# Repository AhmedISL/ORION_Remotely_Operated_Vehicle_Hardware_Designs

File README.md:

# ORION Remotely Operated Vehicle Hardware Design

These are the printed circuit boards (PCBs) designed for controlling the Remotely Operated Vehicle (ROV) which participated in the MATE international ROV competition 2019 and won the 7th place internationally and the 1st place locally and regionally.

## The electrical system is integrated using 4 main PCBs:
> ###### 1- **2** PCBs for the power management.
> ###### 2- **2** PCBs for the communication system and actuators' control.

***Power management PCBs' specifications:***
> ###### 1- Single layer.
> ###### 2- Voltage input range from 48V to 36V. 
> ###### 3- Over-current, voltage and thermal safety system

***Communication and actuators' control PCBs' specification:***
> ###### 1- Single layer.
> ###### 2- Voltage input range from 12V to 9V.
> ###### 3- The required voltage output with 99% efficiency
> ###### 4- Data transferring capability over Bluetooth/USB serial.

# Electronics' Enclosure Assembly

# Board I

# Board II

# Board 2

# Board 3

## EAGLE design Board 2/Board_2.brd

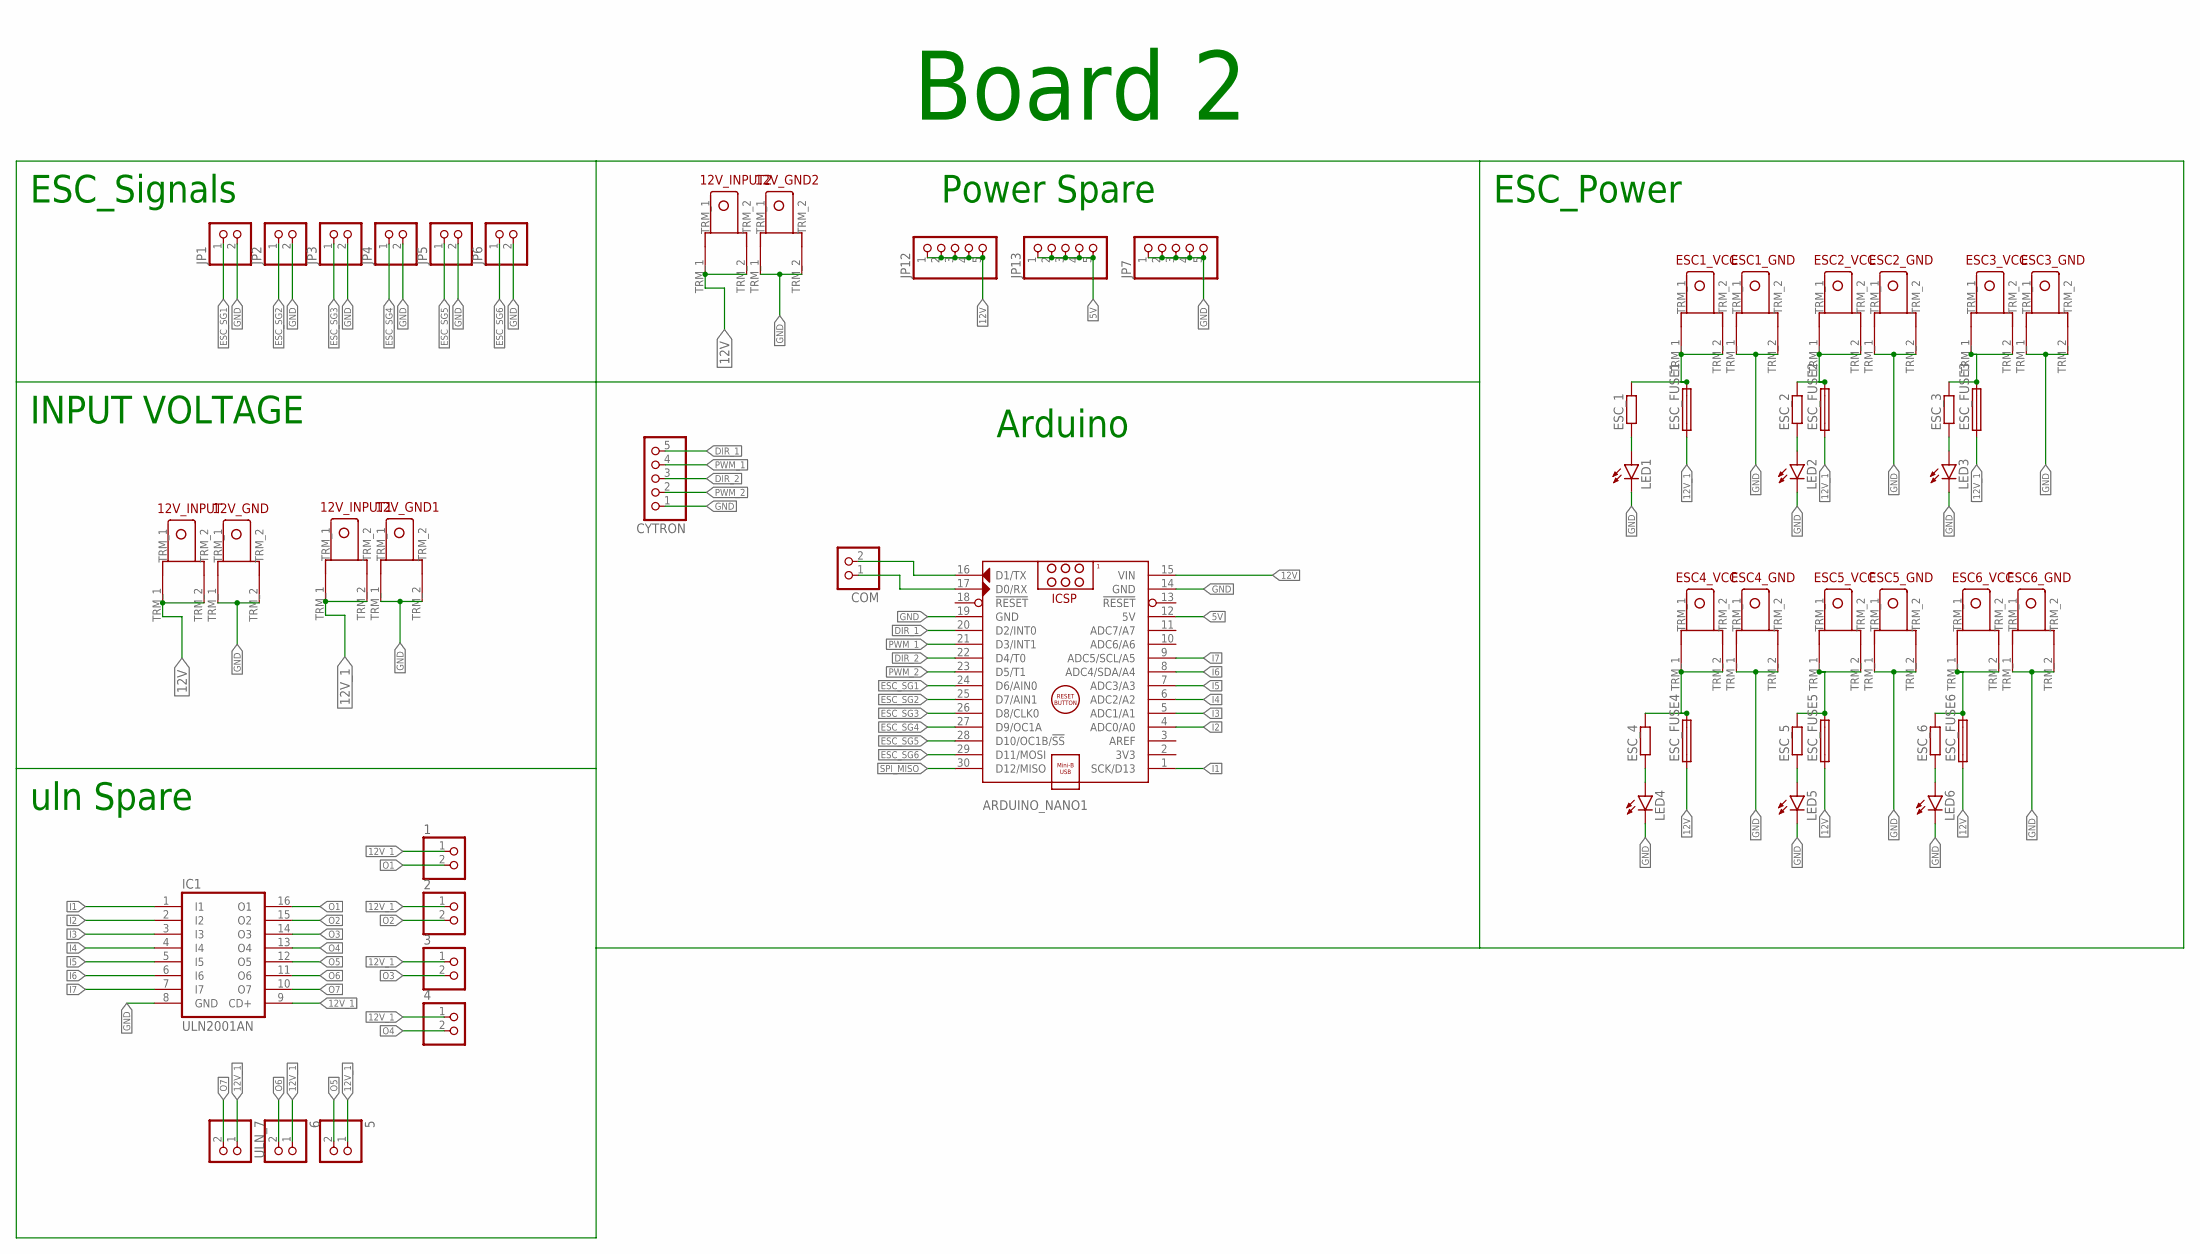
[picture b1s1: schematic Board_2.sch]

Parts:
1, 2, 3, 4, 5, 6: PINHD-1X2; 1X02
12V_GND, 12V_GND1, 12V_GND2, 12V_INPUT, 12V_INPUT1, 12V_INPUT2: TERMINAL_EDITED
ARDUINO_NANO1: ARDUINO_NANO
COM: PINHD-1X2; 1X02
CYTRON: PINHD-1X5; 1X05
ESC1_GND, ESC1_VCC, ESC2_GND, ESC2_VCC, ESC3_GND, ESC3_VCC, ESC4_GND, ESC4_VCC, ESC5_GND, ESC5_VCC, ESC6_GND, ESC6_VCC: TERMINAL_EDITED
ESC_1, ESC_2, ESC_3, ESC_4, ESC_5, ESC_6: RESISTOR; 0207/10
ESC_FUSE1, ESC_FUSE2, ESC_FUSE3, ESC_FUSE4, ESC_FUSE5, ESC_FUSE6: FUSE; SH22,5A
IC1: ULN2001AN; DIL16
JP1, JP2, JP3, JP4, JP5, JP6: PINHD-1X2; 1X02
JP7, JP12, JP13: PINHD-1X5; 1X05
LED1, LED2, LED3, LED4, LED5, LED6: LED5MM
ULN_7: PINHD-1X2; 1X02

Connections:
5V: ARDUINO_NANO1.12 (5V), JP13.1, JP13.2, JP13.3, JP13.4, JP13.5
12V: 12V_INPUT.TRM_1, 12V_INPUT.TRM_2, 12V_INPUT2.TRM_1, 12V_INPUT2.TRM_2, ARDUINO_NANO1.15 (VIN), ESC_FUSE4.1, ESC_FUSE5.1, ESC_FUSE6.1, JP12.1, JP12.2, JP12.3, JP12.4, JP12.5
12V_1: 1.1, 2.1, 3.1, 4.1, 5.1, 6.1, 12V_INPUT1.TRM_1, 12V_INPUT1.TRM_2, ESC_FUSE1.1, ESC_FUSE2.1, ESC_FUSE3.1, IC1.9 (CD+), ULN_7.1
DIR_1: ARDUINO_NANO1.20 (D2/INT0), CYTRON.5
DIR_2: ARDUINO_NANO1.22 (D4/T0), CYTRON.3
ESC_SG1: ARDUINO_NANO1.24 (D6/AIN0), JP1.1
ESC_SG2: ARDUINO_NANO1.25 (D7/AIN1), JP2.1
ESC_SG3: ARDUINO_NANO1.26 (D8/CLK0), JP3.1
ESC_SG4: ARDUINO_NANO1.27 (D9/OC1A), JP4.1
ESC_SG5: ARDUINO_NANO1.28 (D10/OC1B/!SS), JP5.1
ESC_SG6: ARDUINO_NANO1.29 (D11/MOSI), JP6.1
GND: 12V_GND.TRM_1, 12V_GND.TRM_2, 12V_GND1.TRM_1, 12V_GND1.TRM_2, 12V_GND2.TRM_1, 12V_GND2.TRM_2, ARDUINO_NANO1.14 (GND), ARDUINO_NANO1.19 (GND), CYTRON.1, ESC1_GND.TRM_1, ESC1_GND.TRM_2, ESC2_GND.TRM_1, ESC2_GND.TRM_2, ESC3_GND.TRM_1, ESC3_GND.TRM_2, ESC4_GND.TRM_1, ESC4_GND.TRM_2, ESC5_GND.TRM_1, ESC5_GND.TRM_2, ESC6_GND.TRM_1, ESC6_GND.TRM_2, IC1.8 (GND), JP1.2, JP2.2, JP3.2, JP4.2, JP5.2, JP6.2, JP7.1, JP7.2, JP7.3, JP7.4, JP7.5, LED1.K (C), LED2.K (C), LED3.K (C), LED4.K (C), LED5.K (C), LED6.K (C)
I1: ARDUINO_NANO1.1 (SCK/D13), IC1.1 (I1)
I2: ARDUINO_NANO1.4 (ADC0/A0), IC1.2 (I2)
I3: ARDUINO_NANO1.5 (ADC1/A1), IC1.3 (I3)
I4: ARDUINO_NANO1.6 (ADC2/A2), IC1.4 (I4)
I5: ARDUINO_NANO1.7 (ADC3/A3), IC1.5 (I5)
I6: ARDUINO_NANO1.8 (ADC4/SDA/A4), IC1.6 (I6)
I7: ARDUINO_NANO1.9 (ADC5/SCL/A5), IC1.7 (I7)
unnamed: ESC1_VCC.TRM_1, ESC1_VCC.TRM_2, ESC_1.2, ESC_FUSE1.2
unnamed: ESC2_VCC.TRM_1, ESC2_VCC.TRM_2, ESC_2.2, ESC_FUSE2.2
unnamed: ARDUINO_NANO1.17 (D0/RX), COM.1
unnamed: ARDUINO_NANO1.16 (D1/TX), COM.2
unnamed: ESC3_VCC.TRM_1, ESC3_VCC.TRM_2, ESC_3.2, ESC_FUSE3.2
unnamed: ESC4_VCC.TRM_1, ESC4_VCC.TRM_2, ESC_4.2, ESC_FUSE4.2
unnamed: ESC_1.1, LED1.A
unnamed: ESC5_VCC.TRM_1, ESC5_VCC.TRM_2, ESC_5.2, ESC_FUSE5.2
unnamed: ESC_2.1, LED2.A
unnamed: ESC6_VCC.TRM_1, ESC6_VCC.TRM_2, ESC_6.2, ESC_FUSE6.2
unnamed: ESC_3.1, LED3.A
unnamed: ESC_4.1, LED4.A
unnamed: ESC_5.1, LED5.A
unnamed: ESC_6.1, LED6.A
O1: 1.2, IC1.16 (O1)
O2: 2.2, IC1.15 (O2)
O3: 3.2, IC1.14 (O3)
O4: 4.2, IC1.13 (O4)
O5: 5.2, IC1.12 (O5)
O6: 6.2, IC1.11 (O6)
O7: IC1.10 (O7), ULN_7.2
PWM_1: ARDUINO_NANO1.21 (D3/INT1), CYTRON.4
PWM_2: ARDUINO_NANO1.23 (D5/T1), CYTRON.2
SPI_MISO: ARDUINO_NANO1.30 (D12/MISO)

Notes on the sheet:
ESC_Signals
uln Spare
INPUT VOLTAGE
Arduino
Power Spare
ESC_Power
Board 2

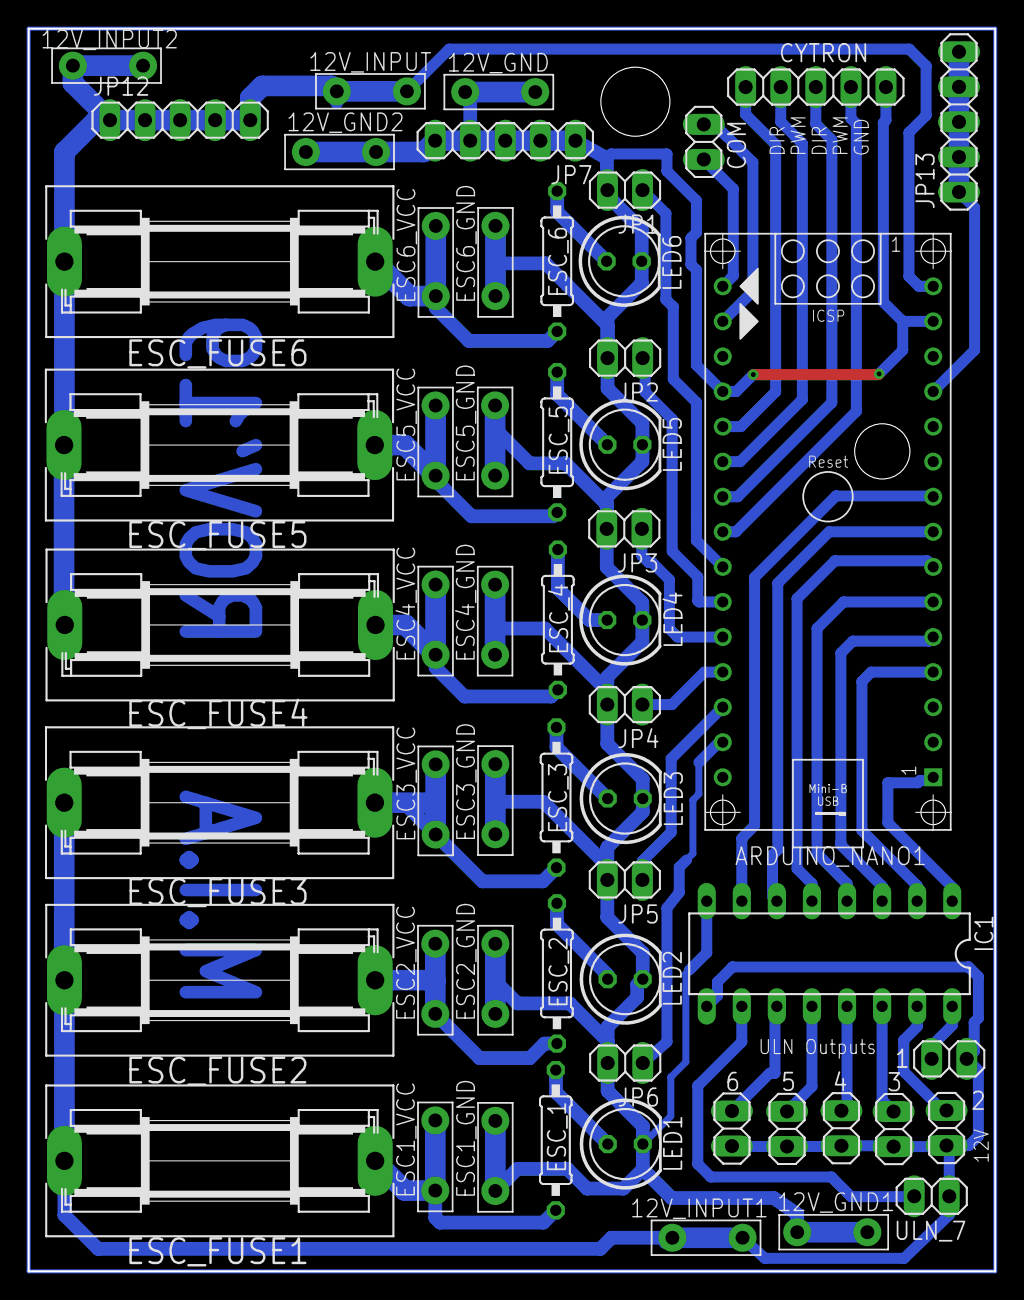
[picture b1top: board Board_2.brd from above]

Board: 2 copper layers, 70.0 x 90.0 mm, 56 parts (0 on the bottom side), 42 nets.

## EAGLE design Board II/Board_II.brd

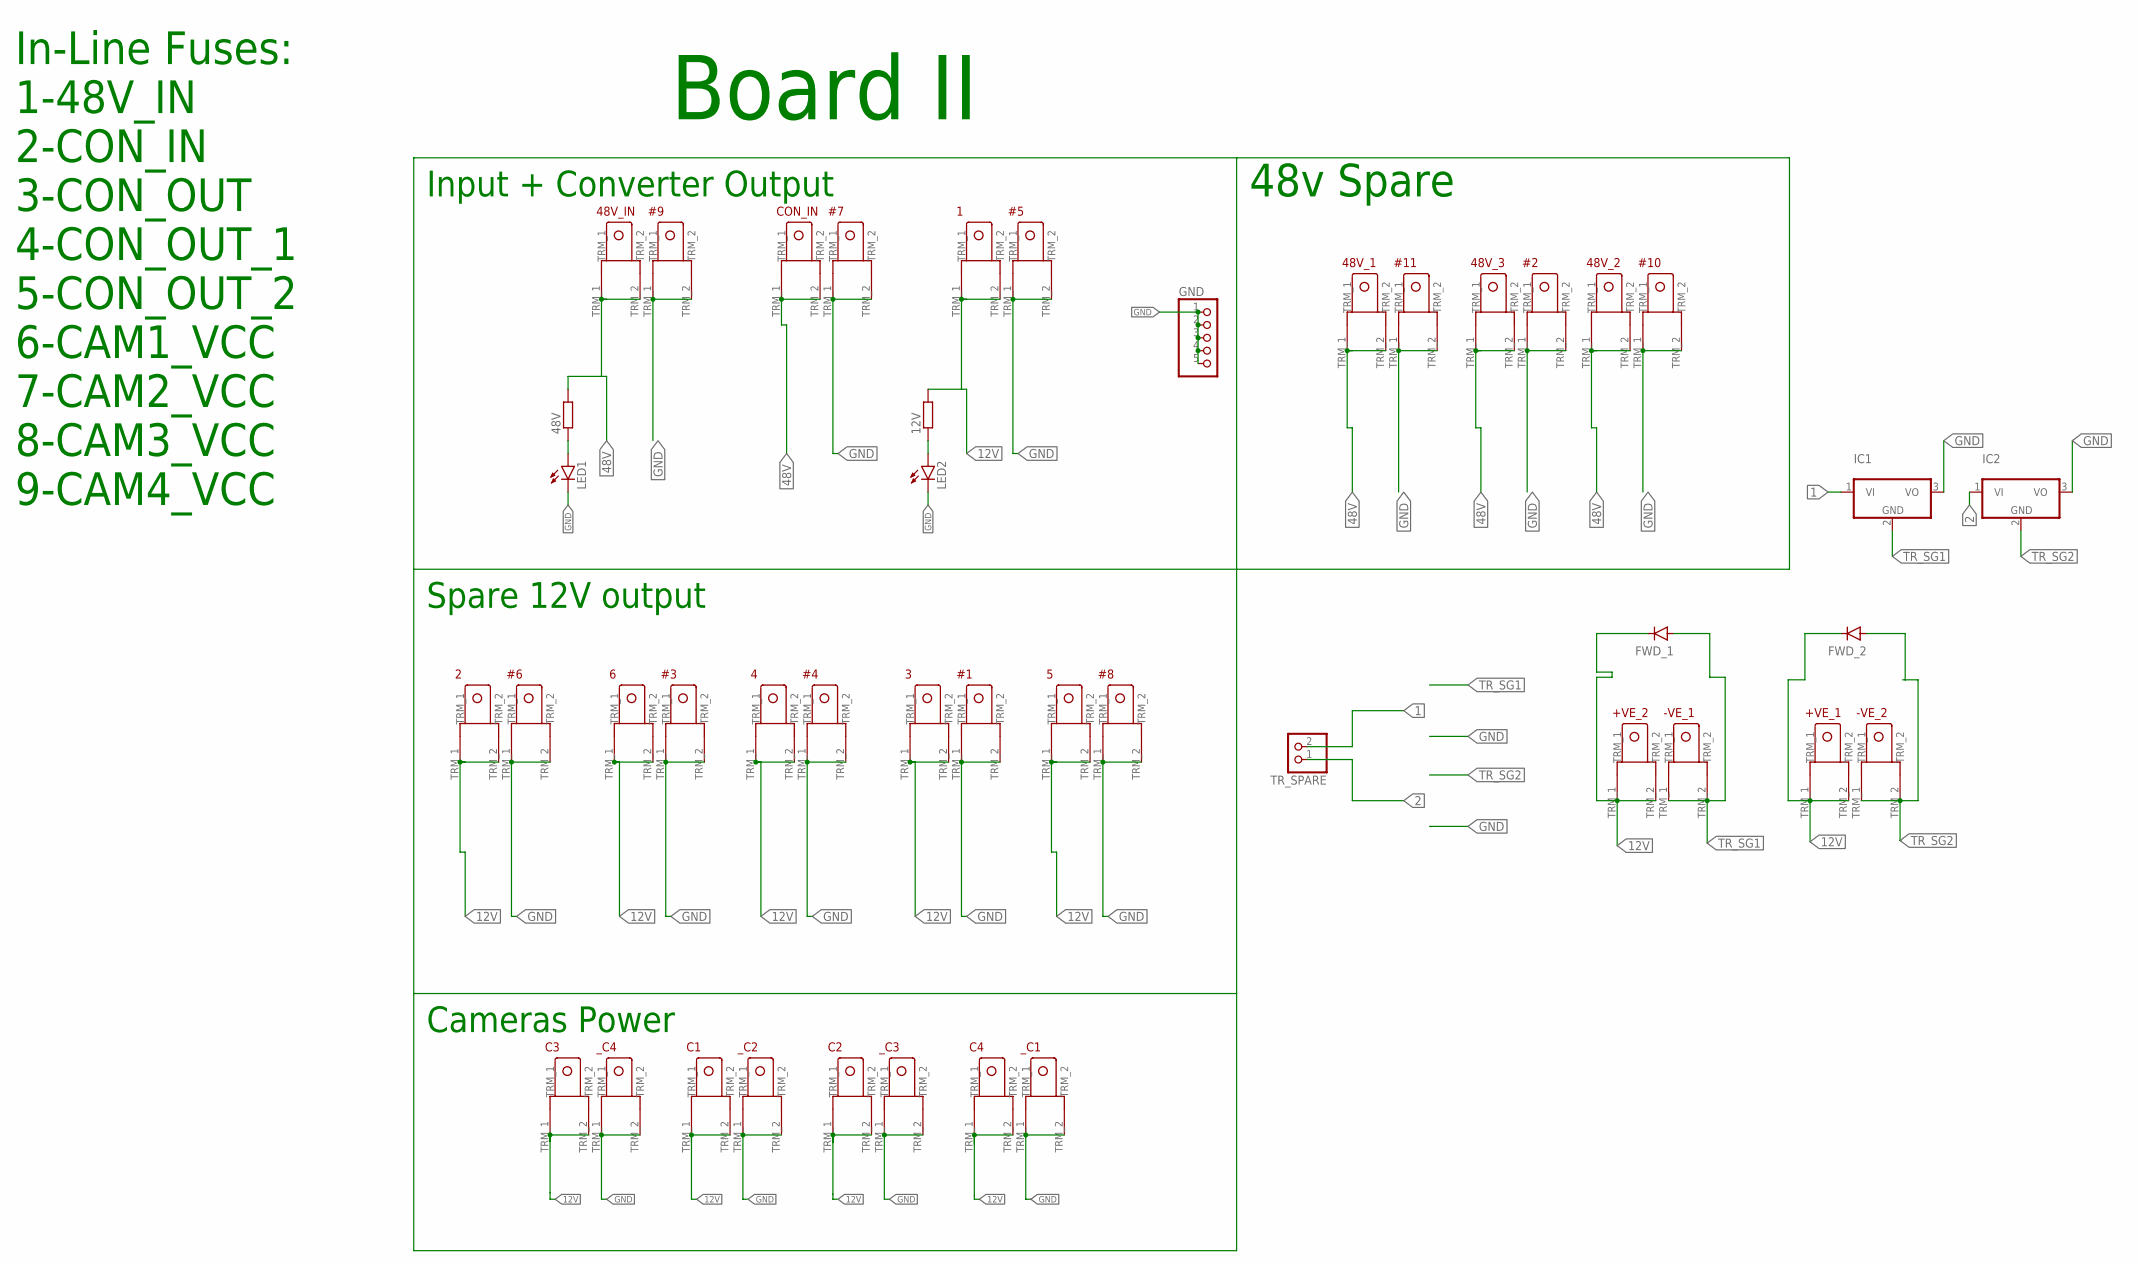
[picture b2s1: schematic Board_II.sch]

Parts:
1, 2, 3, 4, 5, 6, 48V_1, 48V_2, 48V_3, 48V_IN: TERMINAL_EDITED
12V, 48V: RESISTOR; 0207/10
#1, #2, #3, #4, #5, #6, #7, #8, #9, #10, #11: TERMINAL_EDITED
+VE_1, +VE_2: TERMINAL_EDITED
-VE_1, -VE_2: TERMINAL_EDITED
C1, C2, C3, C4: TERMINAL_EDITED
CON_IN: TERMINAL_EDITED
FWD_1, FWD_2: DIODE; DO35-10
GND: PINHD-1X5; 1X05
IC1, IC2: 7805_REG; TO220V
LED1, LED2: LED5MM
TR_SPARE: PINHD-1X2; 1X02
_C1, _C2, _C3, _C4: TERMINAL_EDITED

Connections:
1: IC1.1 (VI), TR_SPARE.2
2: IC2.1 (VI), TR_SPARE.1
12V: 1.TRM_1, 1.TRM_2, 2.TRM_1, 2.TRM_2, 3.TRM_1, 3.TRM_2, 4.TRM_1, 4.TRM_2, 5.TRM_1, 5.TRM_2, 6.TRM_1, 6.TRM_2, 12V.2, +VE_1.TRM_1, +VE_1.TRM_2, +VE_2.TRM_1, +VE_2.TRM_2, C1.TRM_1, C1.TRM_2, C2.TRM_1, C2.TRM_2, C3.TRM_1, C3.TRM_2, C4.TRM_1, C4.TRM_2, FWD_1.C, FWD_2.C
48V: 48V.2, 48V_1.TRM_1, 48V_1.TRM_2, 48V_2.TRM_1, 48V_2.TRM_2, 48V_3.TRM_1, 48V_3.TRM_2, 48V_IN.TRM_1, 48V_IN.TRM_2, CON_IN.TRM_1, CON_IN.TRM_2
GND: #1.TRM_1, #1.TRM_2, #2.TRM_1, #2.TRM_2, #3.TRM_1, #3.TRM_2, #4.TRM_1, #4.TRM_2, #5.TRM_1, #5.TRM_2, #6.TRM_1, #6.TRM_2, #7.TRM_1, #7.TRM_2, #8.TRM_1, #8.TRM_2, #9.TRM_1, #9.TRM_2, #10.TRM_1, #10.TRM_2, #11.TRM_1, #11.TRM_2, GND.1, GND.2, GND.3, GND.4, GND.5, IC1.3 (VO), IC2.3 (VO), LED1.K (C), LED2.K (C), _C1.TRM_1, _C1.TRM_2, _C2.TRM_1, _C2.TRM_2, _C3.TRM_1, _C3.TRM_2, _C4.TRM_1, _C4.TRM_2
unnamed: 48V.1, LED1.A
unnamed: 12V.1, LED2.A
TR_SG1: -VE_1.TRM_1, -VE_1.TRM_2, FWD_1.A, IC1.2 (GND)
TR_SG2: -VE_2.TRM_1, -VE_2.TRM_2, FWD_2.A, IC2.2 (GND)

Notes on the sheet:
Input + Converter Output
Spare 12V output
Cameras Power
Board II
In-Line Fuses: 1-48V_IN 2-CON_IN 3-CON_OUT 4-CON_OUT_1 5-CON_OUT_2 6-CAM1_VCC 7-CAM2_VCC 8-CAM3_VCC 9-CAM4_VCC
48v Spare

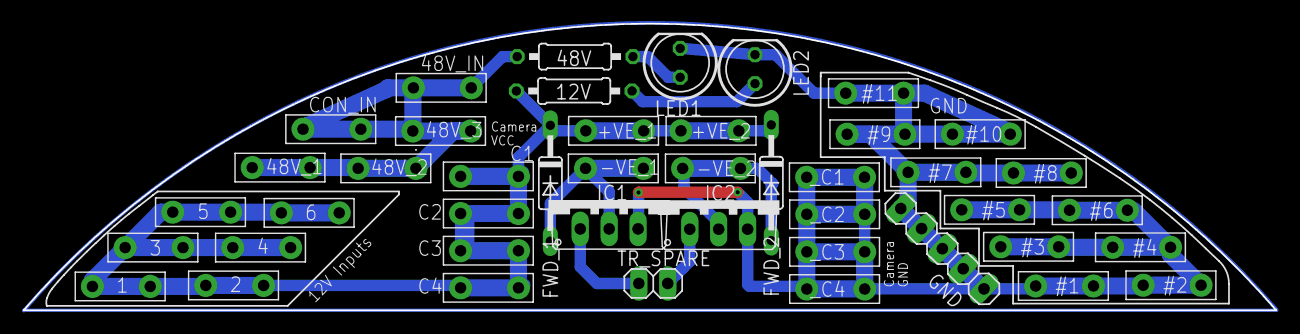
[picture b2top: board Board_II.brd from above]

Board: 2 copper layers, 110.0 x 25.2 mm, 44 parts (0 on the bottom side), 9 nets.

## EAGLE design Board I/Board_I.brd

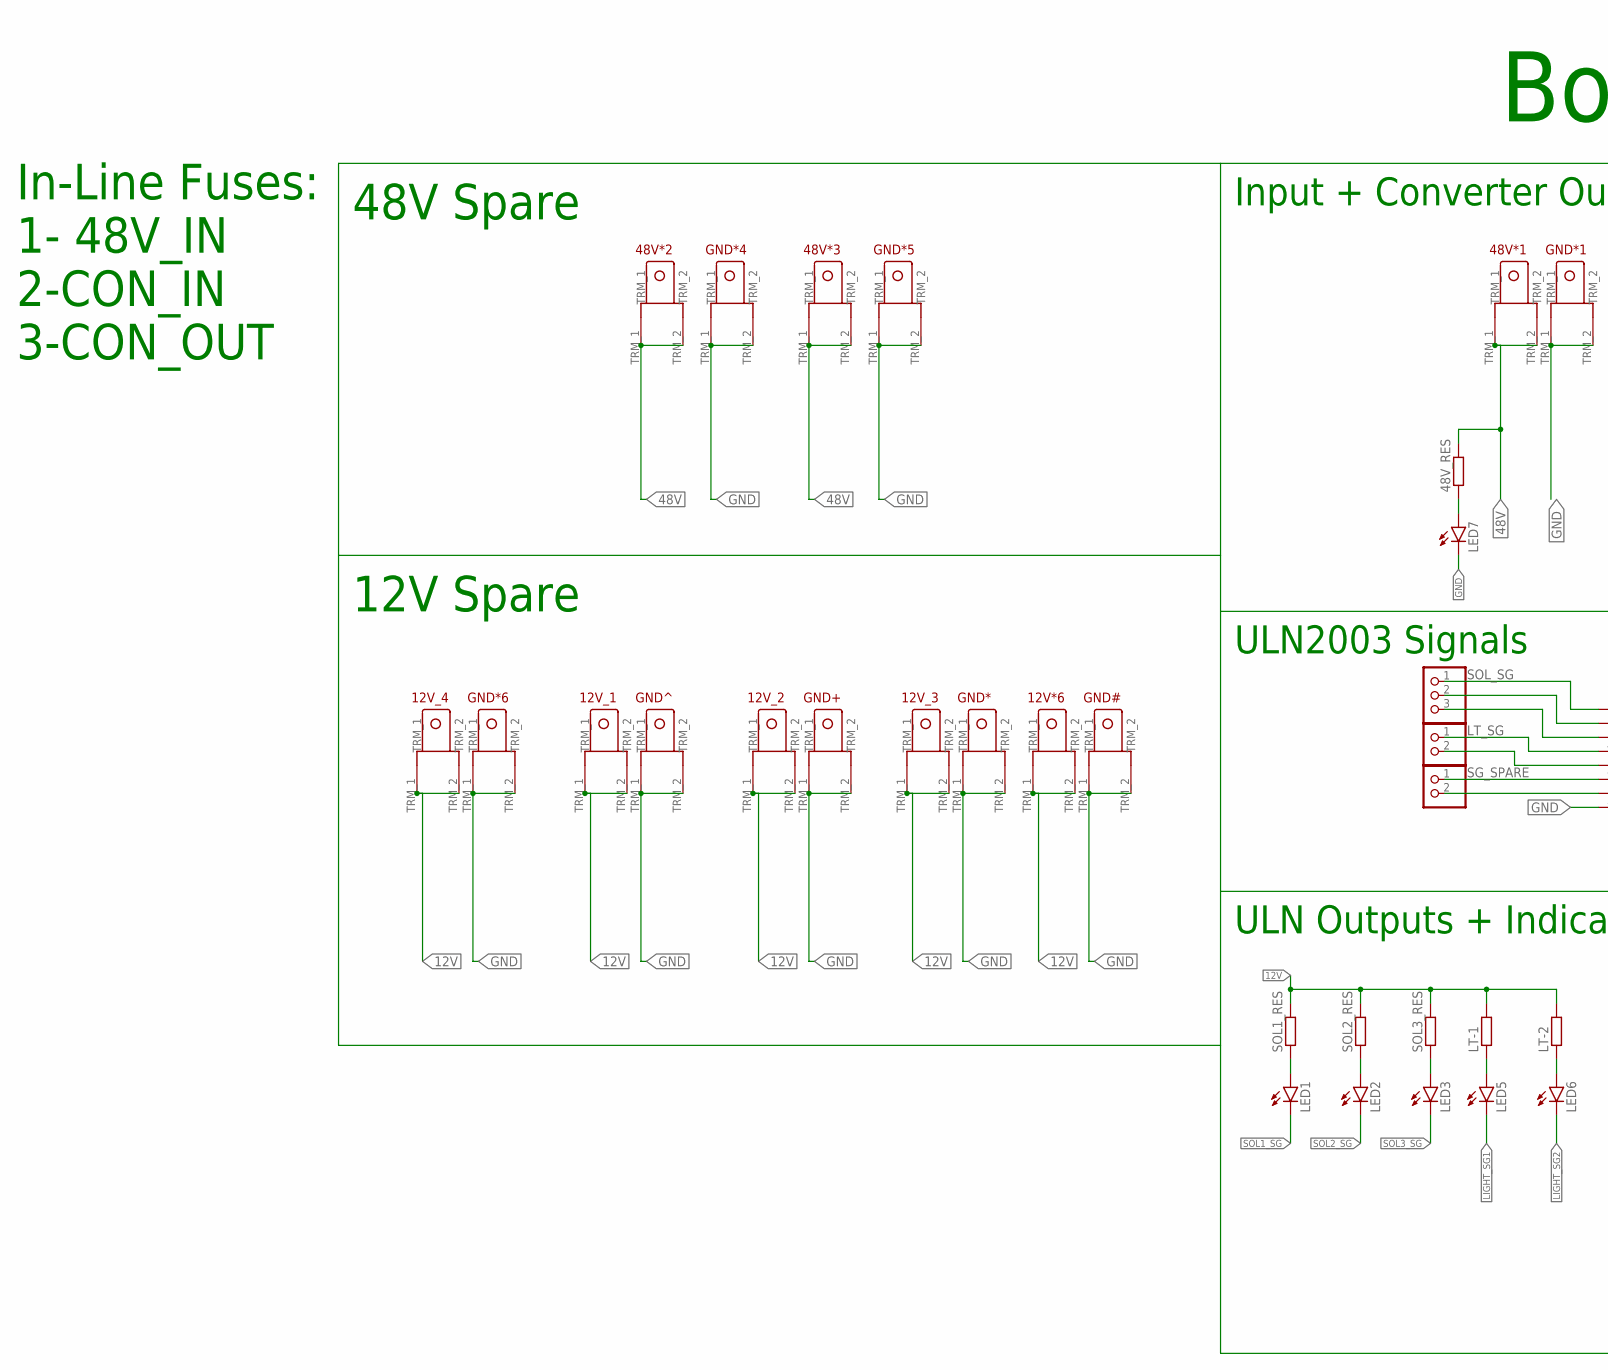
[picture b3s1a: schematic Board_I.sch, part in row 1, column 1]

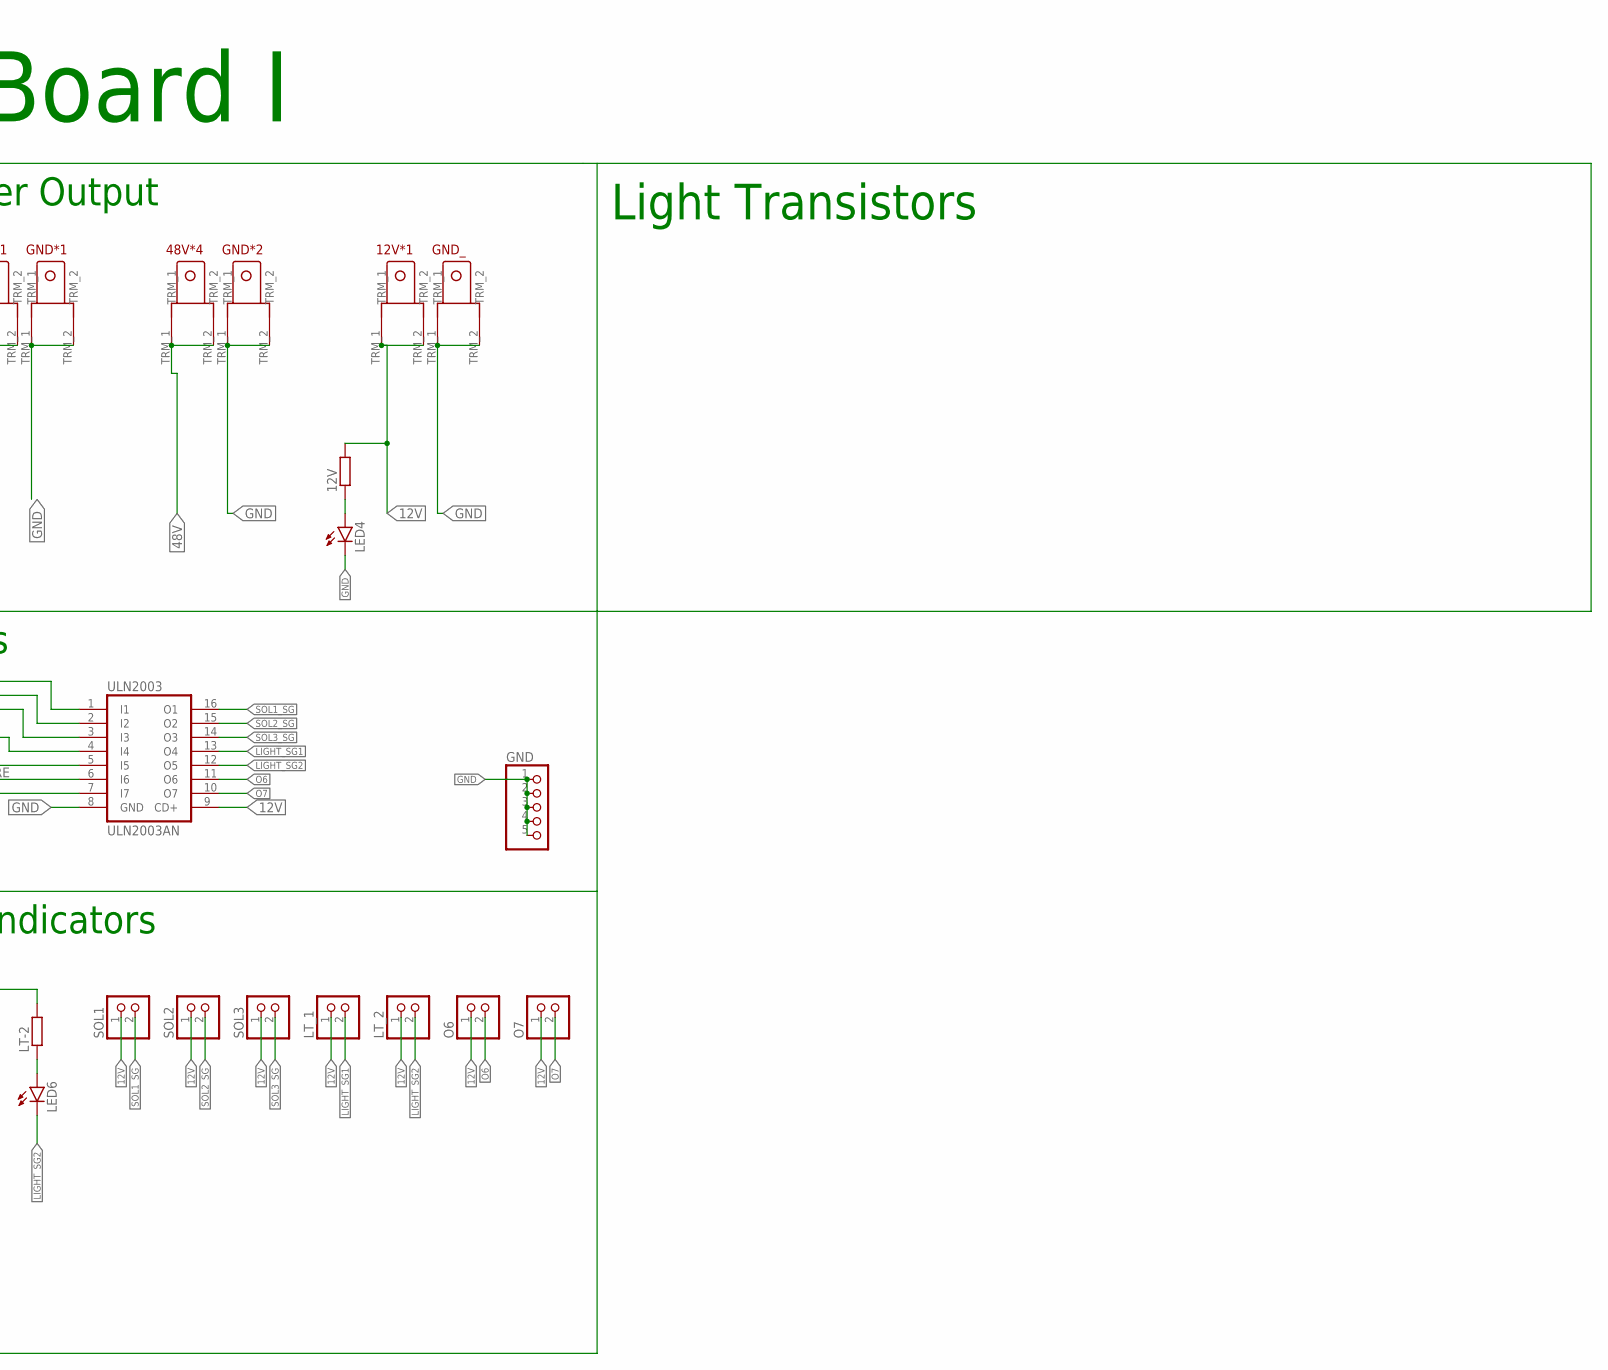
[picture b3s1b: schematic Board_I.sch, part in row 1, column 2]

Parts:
12V, 48V_RES: RESISTOR; 0207/10
12V*1, 12V*6, 12V_1, 12V_2, 12V_3, 12V_4, 48V*1, 48V*2, 48V*3, 48V*4: TERMINAL_EDITED
GND: PINHD-1X5; 1X05
GND#: TERMINAL_EDITED
GND*, GND*1, GND*2, GND*4, GND*5, GND*6: TERMINAL_EDITED
GND+: TERMINAL_EDITED
GND^: TERMINAL_EDITED
GND_: TERMINAL_EDITED
LED1, LED2, LED3, LED4, LED5, LED6, LED7: LED5MM
LT-1, LT-2: RESISTOR; 0207/10
LT_1, LT_2: PINHD-1X2; 1X02
LT_SG: PINHD-1X2; 1X02
O6, O7: PINHD-1X2; 1X02
SG_SPARE: PINHD-1X2; 1X02
SOL1, SOL2, SOL3: PINHD-1X2; 1X02
SOL1_RES, SOL2_RES, SOL3_RES: RESISTOR; 0207/10
SOL_SG: PINHD-1X3; 1X03
ULN2003: ULN2003AN; DIL16

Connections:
12V: 12V.2, 12V*1.TRM_1, 12V*1.TRM_2, 12V*6.TRM_1, 12V*6.TRM_2, 12V_1.TRM_1, 12V_1.TRM_2, 12V_2.TRM_1, 12V_2.TRM_2, 12V_3.TRM_1, 12V_3.TRM_2, 12V_4.TRM_1, 12V_4.TRM_2, LT-1.2, LT-2.2, LT_1.1, LT_2.1, O6.1, O7.1, SOL1.1, SOL1_RES.2, SOL2.1, SOL2_RES.2, SOL3.1, SOL3_RES.2, ULN2003.9 (CD+)
48V: 48V*1.TRM_1, 48V*1.TRM_2, 48V*2.TRM_1, 48V*2.TRM_2, 48V*3.TRM_1, 48V*3.TRM_2, 48V*4.TRM_1, 48V*4.TRM_2, 48V_RES.2
GND: GND.1, GND.2, GND.3, GND.4, GND.5, GND#.TRM_1, GND#.TRM_2, GND*.TRM_1, GND*.TRM_2, GND*1.TRM_1, GND*1.TRM_2, GND*2.TRM_1, GND*2.TRM_2, GND*4.TRM_1, GND*4.TRM_2, GND*5.TRM_1, GND*5.TRM_2, GND*6.TRM_1, GND*6.TRM_2, GND+.TRM_1, GND+.TRM_2, GND^.TRM_1, GND^.TRM_2, GND_.TRM_1, GND_.TRM_2, LED4.K (C), LED7.K (C), ULN2003.8 (GND)
LIGHT_SG1: LED5.K (C), LT_1.2, ULN2003.13 (O4)
LIGHT_SG2: LED6.K (C), LT_2.2, ULN2003.12 (O5)
unnamed: LED6.A, LT-2.1
unnamed: SOL_SG.1, ULN2003.1 (I1)
unnamed: 48V_RES.1, LED7.A
unnamed: SOL_SG.2, ULN2003.2 (I2)
unnamed: 12V.1, LED4.A
unnamed: SOL_SG.3, ULN2003.3 (I3)
unnamed: LED1.A, SOL1_RES.1
unnamed: LED2.A, SOL2_RES.1
unnamed: LED3.A, SOL3_RES.1
unnamed: LT_SG.1, ULN2003.4 (I4)
unnamed: LT_SG.2, ULN2003.5 (I5)
unnamed: SG_SPARE.1, ULN2003.6 (I6)
unnamed: SG_SPARE.2, ULN2003.7 (I7)
unnamed: LED5.A, LT-1.1
O6: O6.2, ULN2003.11 (O6)
O7: O7.2, ULN2003.10 (O7)
SOL1_SG: LED1.K (C), SOL1.2, ULN2003.16 (O1)
SOL2_SG: LED2.K (C), SOL2.2, ULN2003.15 (O2)
SOL3_SG: LED3.K (C), SOL3.2, ULN2003.14 (O3)

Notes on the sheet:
Input + Converter Output
ULN2003 Signals
ULN Outputs + Indicators
Board I
In-Line Fuses: 1- 48V_IN 2-CON_IN 3-CON_OUT
48V Spare
12V Spare
Light Transistors

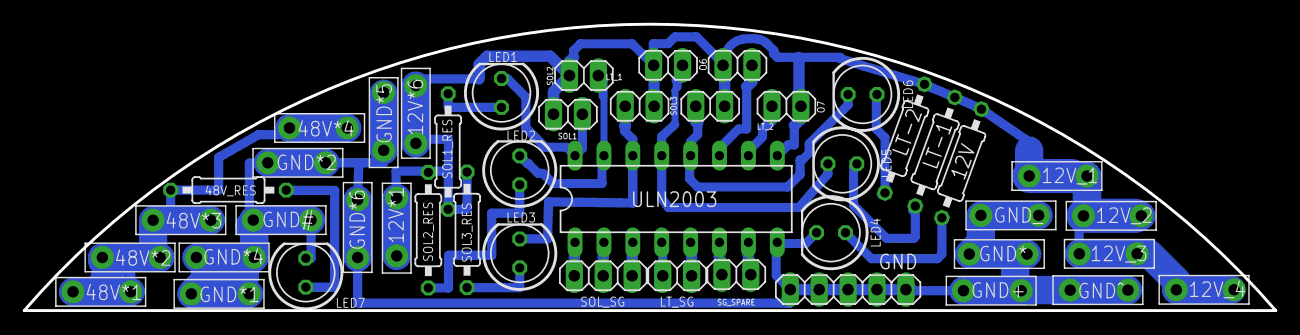
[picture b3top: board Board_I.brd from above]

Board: 2 copper layers, 110.0 x 25.2 mm, 46 parts (0 on the bottom side), 24 nets.

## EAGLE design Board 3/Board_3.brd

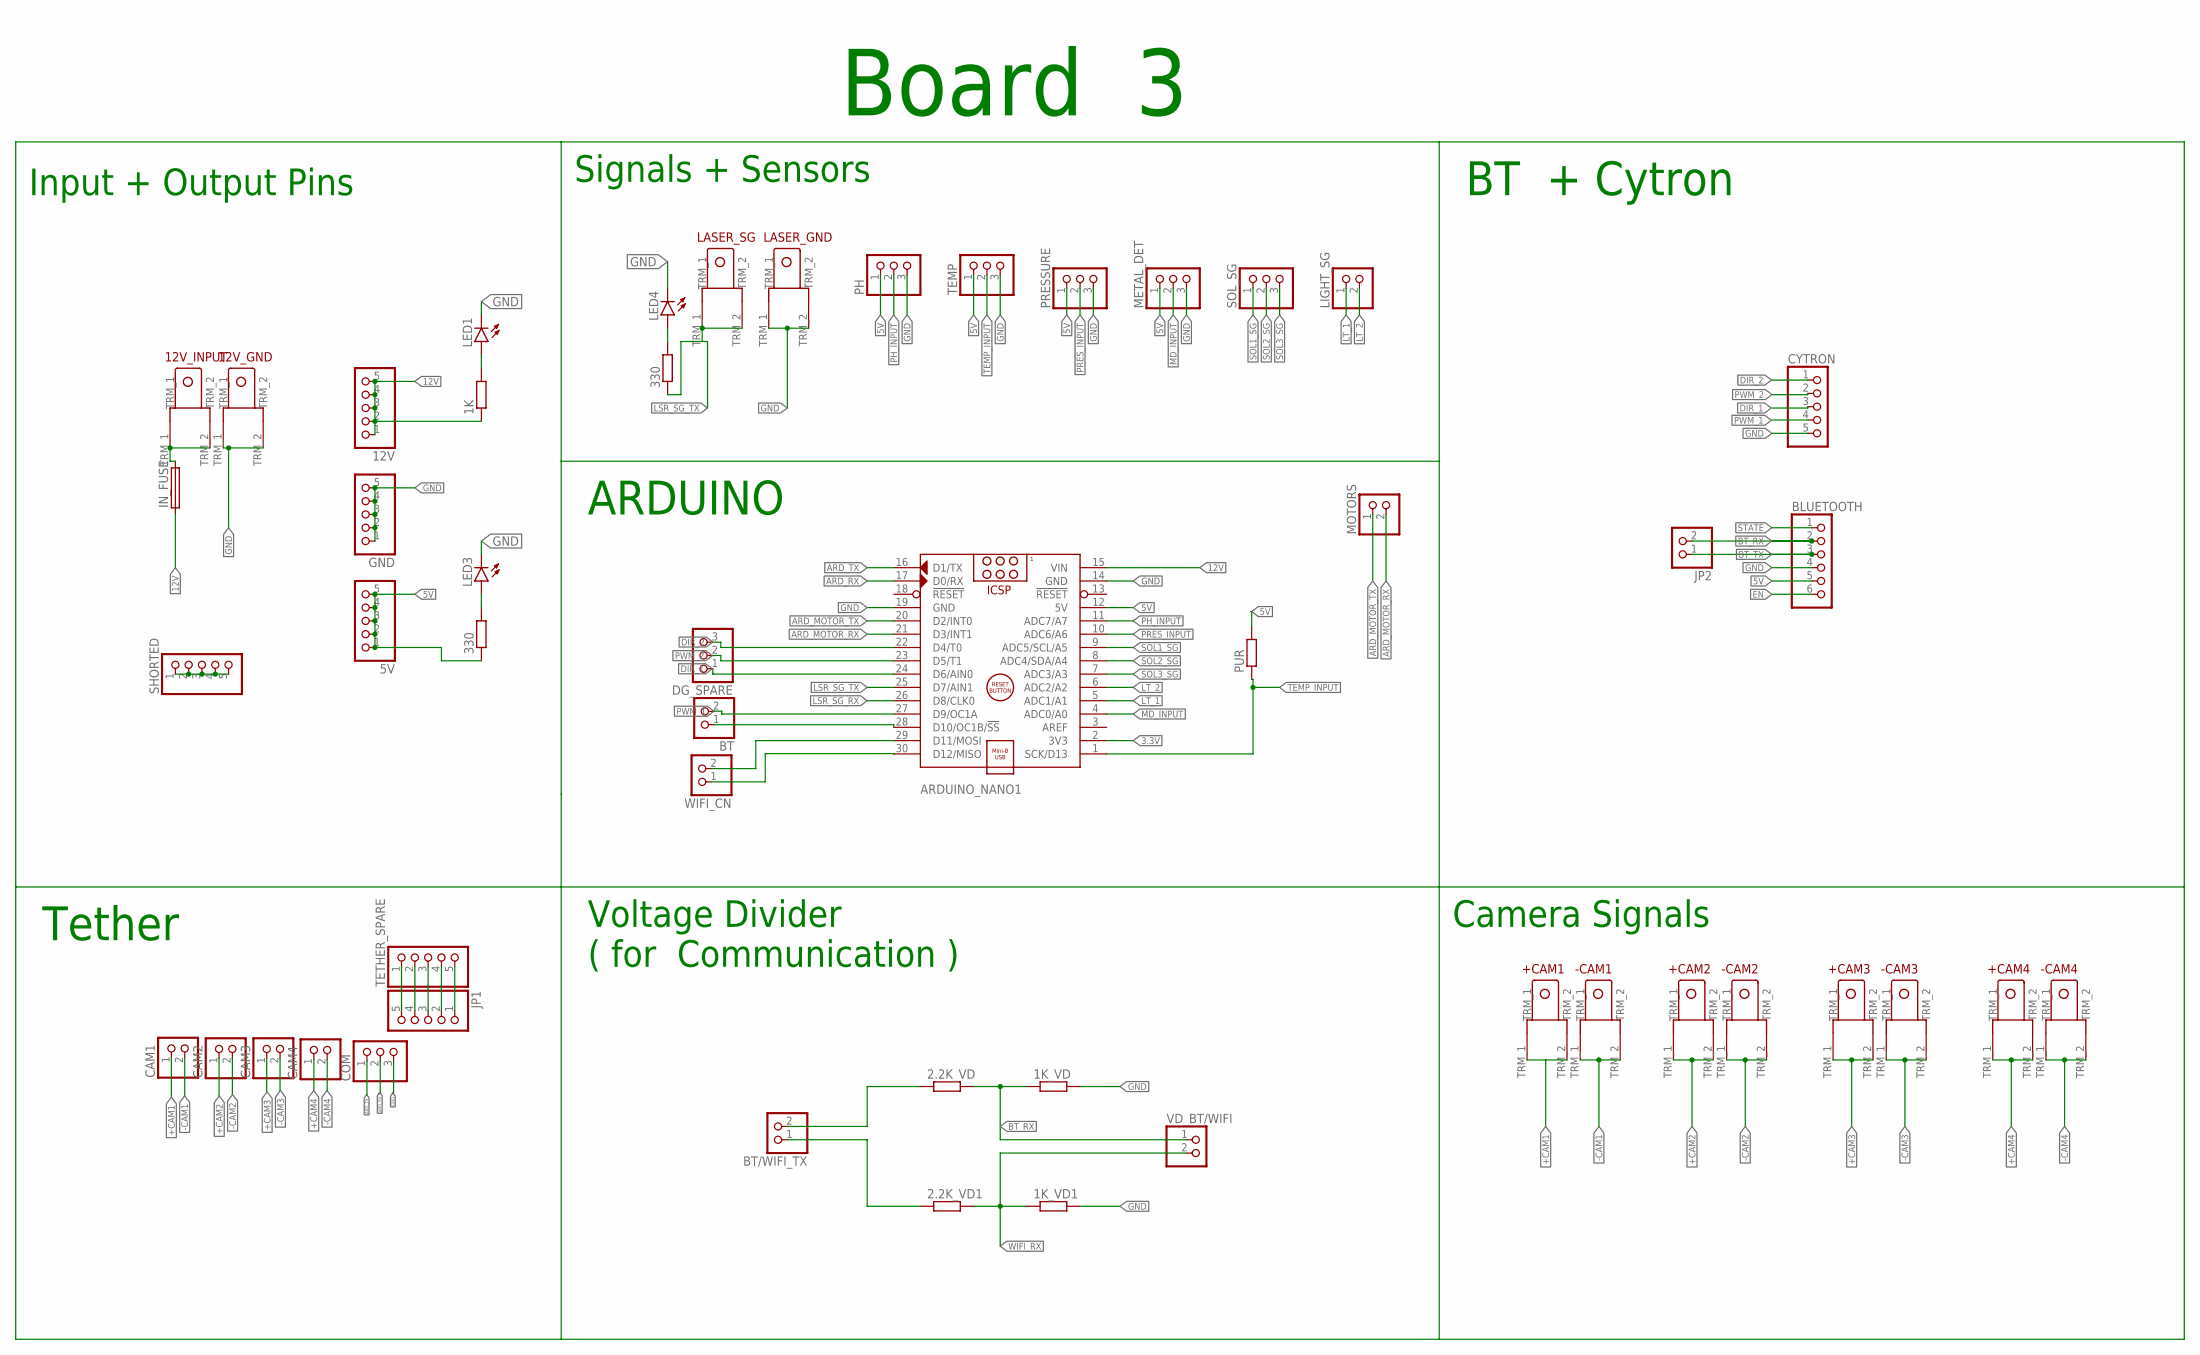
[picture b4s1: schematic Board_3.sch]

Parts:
1K, 1K_VD, 1K_VD1, 2.2K_VD, 2.2K_VD1, 330, 330_: RESISTOR; 0207/10
5V, 12V: PINHD-1X5; 1X05
12V_GND, 12V_INPUT: TERMINAL_EDITED
+CAM1, +CAM2, +CAM3, +CAM4: TERMINAL_EDITED
-CAM1, -CAM2, -CAM3, -CAM4: TERMINAL_EDITED
ARDUINO_NANO1: ARDUINO_NANO
BLUETOOTH: BLUETOOTH_HC-05; 1X06
BT: PINHD-1X2; 1X02
BT/WIFI_TX: PINHD-1X2; 1X02
CAM1, CAM2, CAM3, CAM4: PINHD-1X2; 1X02
COM: PINHD-1X3; 1X03
CYTRON: PINHD-1X5; 1X05
DG_SPARE: PINHD-1X3; 1X03
GND: PINHD-1X5; 1X05
IN_FUSE: FUSE; SH22,5A
JP1: PINHD-1X5; 1X05
JP2: PINHD-1X2; 1X02
LASER_GND: TERMINAL_EDITED
LASER_SG: TERMINAL_EDITED
LED1, LED3, LED4: LED5MM
LIGHT_SG: PINHD-1X2; 1X02
METAL_DET: PINHD-1X3; 1X03
MOTORS: PINHD-1X2; 1X02
PH: PINHD-1X3; 1X03
PRESSURE: PINHD-1X3; 1X03
PUR: RESISTOR; 0207/10
SHORTED: PINHD-1X5; 1X05
SOL_SG: PINHD-1X3; 1X03
TEMP: PINHD-1X3; 1X03
TETHER_SPARE: PINHD-1X5; 1X05
VD_BT/WIFI: PINHD-1X2; 1X02
WIFI_CN: PINHD-1X2; 1X02

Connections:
3.3V: ARDUINO_NANO1.2 (3V3)
5V: 5V.1, 5V.2, 5V.3, 5V.4, 5V.5, 330.1, ARDUINO_NANO1.12 (5V), BLUETOOTH.5, METAL_DET.1, PH.1, PRESSURE.1, PUR.2, TEMP.1
12V: 1K.1, 12V.1, 12V.2, 12V.3, 12V.4, 12V.5, ARDUINO_NANO1.15 (VIN), IN_FUSE.1
+CAM1: +CAM1.TRM_1, +CAM1.TRM_2, CAM1.1
+CAM2: +CAM2.TRM_1, +CAM2.TRM_2, CAM2.1
+CAM3: +CAM3.TRM_1, +CAM3.TRM_2, CAM3.1
+CAM4: +CAM4.TRM_1, +CAM4.TRM_2, CAM4.1
-CAM1: -CAM1.TRM_1, -CAM1.TRM_2, CAM1.2
-CAM2: -CAM2.TRM_1, -CAM2.TRM_2, CAM2.2
-CAM3: -CAM3.TRM_1, -CAM3.TRM_2, CAM3.2
-CAM4: -CAM4.TRM_1, -CAM4.TRM_2, CAM4.2
ARD_MOTOR_RX: ARDUINO_NANO1.21 (D3/INT1), MOTORS.2
ARD_MOTOR_TX: ARDUINO_NANO1.20 (D2/INT0), MOTORS.1
ARD_RX: ARDUINO_NANO1.17 (D0/RX), COM.2
ARD_TX: ARDUINO_NANO1.16 (D1/TX), COM.1
BT_RX: 1K_VD.1, 2.2K_VD.2, BLUETOOTH.2, JP2.2, VD_BT/WIFI.1
BT_TX: BLUETOOTH.3, JP2.1
DIR_1: ARDUINO_NANO1.24 (D6/AIN0), CYTRON.3, DG_SPARE.1
DIR_2: ARDUINO_NANO1.22 (D4/T0), CYTRON.1, DG_SPARE.3
EN: BLUETOOTH.6
GND: 1K_VD.2, 1K_VD1.2, 12V_GND.TRM_1, 12V_GND.TRM_2, ARDUINO_NANO1.14 (GND), ARDUINO_NANO1.19 (GND), BLUETOOTH.4, COM.3, CYTRON.5, GND.1, GND.2, GND.3, GND.4, GND.5, LASER_GND.TRM_1, LASER_GND.TRM_2, LED1.K (C), LED3.K (C), LED4.K (C), METAL_DET.3, PH.3, PRESSURE.3, TEMP.3
LSR_SG_RX: ARDUINO_NANO1.26 (D8/CLK0)
LSR_SG_TX: 330_.1, ARDUINO_NANO1.25 (D7/AIN1), LASER_SG.TRM_1, LASER_SG.TRM_2
LT_1: ARDUINO_NANO1.5 (ADC1/A1), LIGHT_SG.1
LT_2: ARDUINO_NANO1.6 (ADC2/A2), LIGHT_SG.2
MD_INPUT: ARDUINO_NANO1.4 (ADC0/A0), METAL_DET.2
unnamed: JP1.5, TETHER_SPARE.1
unnamed: JP1.4, TETHER_SPARE.2
unnamed: JP1.3, TETHER_SPARE.3
unnamed: JP1.2, TETHER_SPARE.4
unnamed: JP1.1, TETHER_SPARE.5
unnamed: ARDUINO_NANO1.28 (D10/OC1B/!SS), BT.1
unnamed: ARDUINO_NANO1.29 (D11/MOSI), WIFI_CN.2
unnamed: ARDUINO_NANO1.30 (D12/MISO), WIFI_CN.1
unnamed: SHORTED.1, SHORTED.2, SHORTED.3, SHORTED.4, SHORTED.5
unnamed: 330_.2, LED4.A
unnamed: 2.2K_VD.1, BT/WIFI_TX.2
unnamed: 1K.2, LED1.A
unnamed: 2.2K_VD1.1, BT/WIFI_TX.1
unnamed: 330.2, LED3.A
unnamed: 12V_INPUT.TRM_1, 12V_INPUT.TRM_2, IN_FUSE.2
PH_INPUT: ARDUINO_NANO1.11 (ADC7/A7), PH.2
PRES_INPUT: ARDUINO_NANO1.10 (ADC6/A6), PRESSURE.2
PWM_1: ARDUINO_NANO1.27 (D9/OC1A), BT.2, CYTRON.4
PWM_2: ARDUINO_NANO1.23 (D5/T1), CYTRON.2, DG_SPARE.2
SOL1_SG: ARDUINO_NANO1.9 (ADC5/SCL/A5), SOL_SG.1
SOL2_SG: ARDUINO_NANO1.8 (ADC4/SDA/A4), SOL_SG.2
SOL3_SG: ARDUINO_NANO1.7 (ADC3/A3), SOL_SG.3
STATE: BLUETOOTH.1
TEMP_INPUT: ARDUINO_NANO1.1 (SCK/D13), PUR.1, TEMP.2
WIFI_RX: 1K_VD1.1, 2.2K_VD1.2, VD_BT/WIFI.2

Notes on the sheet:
Input + Output Pins
Signals + Sensors
BT + Cytron
ARDUINO
Voltage Divider ( for Communication )
Camera Signals
Tether
Board 3
